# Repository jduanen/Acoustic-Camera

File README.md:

# Acoustic Camera — Project Summary

This project involves the design and implementation of a low-cost,
high-performance acoustic camera: i.e., a microphone array computes a power map
of the sound sources in a video camera's field of view and overlays it on the
video in real time.

Uses of such a device include locating vibration, gas leaks and electrical
breakdown, and as a hearing aid for people who can no longer localize sound
with one functional ear.

One of the top-level objectives for this project is to explore the use of
deep-learning models for this application and compare the performance and cost
with that of traditional DSP-based beamforming algorithms.

A full technical overview of the project can be found in [OVERVIEW.md](./OVERVIEW.md);
see the linked documents for more detail.

The Phase 3 prototype (4x4-mic array) unit looks like this:
<br>

This is an animation of the current state of the Phase 4 (96-mic spiral array) version's PCBs: 

See an example of a commercial product here [Fluke](https://youtu.be/UPVcwDzhBZ8) and a low-cost consumer product here [Fotric](https://youtu.be/MBhJoPzHv2Y)

## How it works

The microphone array samples the sound field at every mic at once. For each candidate direction
(azimuth, elevation), a **steering vector** describes the expected phase pattern across the
mics; a **beamformer** scores each direction against the measured **cross-spectral matrix
(CSM)** and the scores form the energy map overlaid on the video.

Three array properties set performance:

| Property | Controls | Rule |
|---|---|---|
| Aperture *D* | Beam width (resolution) and low-frequency limit | HPBW ≈ 58° × λ/*D*; useful directionality needs *f* > *c*/*D* |
| Minimum mic spacing *d* | High-frequency limit (grating lobes above it) | *f*<sub>Nyq</sub> = *c* / (2*d*) |
| Mic layout and count | Sidelobe level (MSL), SNR | Irregular spacing suppresses aliasing; more mics lower sidelobes |

Other key ideas: far field begins at *r* > 2*D*²/λ; the **point spread function** is how the
array smears a point source; commercial cameras average power incoherently across an octave
band to cut noise. Details: [BACKGROUND.md](./BACKGROUND.md), [MIC_ARRAYS.md](./MIC_ARRAYS.md).

**Algorithms explored** (one per family): Delay-and-Sum (simple, robust, wide beam), MVDR
(adaptive, suppresses interferers), CLEAN-SC (deconvolution, removes PSF artifacts), MUSIC
(subspace, super-resolution when the source count is known). ML methods come in Phase 5.

## Requirements and key design choices

| Parameter | Target |
|---|---|
| Frequency range | 200 Hz: 8 kHz (useful imaging from ~2 kHz) |
| Resolution (HPBW) | ~9.4° @ 8 kHz, ~19° @ 4 kHz, ~82° @ 1 kHz (simulated, Phase 4 array) |
| Distance | ~0.5 m (far-field limit) to ~10 m |
| Field of view | ±45° H, ±30° V, matched to the camera |
| Array | ~300 mm aperture, 96 MEMS mics, Underbrink 12 × 8 log-spiral, 12.94 mm min spacing (Nyquist ≈ 13.3 kHz) |

Why these numbers ([TRADEOFFS.md](./TRADEOFFS.md)):
- **300 mm aperture** is the practical sweet spot: portable, yet ~9° at 8 kHz. 5° at 1 kHz
  would need a ~4 m aperture.
- **96 mics** matches commercial practice (gfai Mikado uses 96 in the same pattern). Mic count
  grows as (aperture/spacing)², so going much smaller in spacing costs ~400+ mics.
- **Underbrink spiral** gave the best sidelobe suppression of all patterns simulated
  (−24.4 dB @ 4 kHz), with circular symmetry.
- **Beamforming grid**: 2–3 points per HPBW is enough. Finer grids cost memory and time
  (the steering matrix dominates) without improving resolution; the 96-mic array needs a
  finer grid than the UMA-16's 0.5°–1°.

## Development phases

Each phase delivers a working end-to-end system ([PLAN.md](./PLAN.md)).

| Phase | Hardware | Goal | Status |
|---|---|---|---|
| 1 | Simulation | Validate algorithms and array geometry | Complete |
| 2 | ReSpeaker XVF3800 (4 mics, 90 mm) | First end-to-end pipeline: capture → beamform → overlay | Complete |
| 3 | miniDSP UMA-16 v2 (16 mics, 126 mm) | 2D (az × el) beamforming, calibration, touch UI | Complete |
| 4 | Custom PCBs (96 mics, 300 mm, FPGA) | Full-performance system | In progress |
| 5 | Phase 3/4 hardware | ML beamformer (PILOT / CRNN) vs CLEAN-SC | Not started |

### Phase 1 — simulation ([PHASE1.md](./PHASE1.md))
- Recommended array: Underbrink 12 × 8, α = 22°, 96 mics, 300 mm, 12.9 mm minimum spacing, alias-free to ~13 kHz.
- HPBW: >180° below 500 Hz, ~82° @ 1 kHz, ~37° @ 2 kHz, ~19° @ 4 kHz, ~9° @ 8 kHz.
- Algorithm choice: CLEAN-SC for real-time single-source display; MVDR for multiple or weak
  sources; MUSIC for closely spaced sources with known count; D&S for lowest latency.
  256 snapshots per CSM.
- Works well: industrial source hunting at 2–8 kHz, multi-source scenes, normal rooms,
  near field at 0.5–3 m. Not suited: below 1 kHz, very reverberant spaces (DRR < 3 dB),
  separating sources on the same bearing, MUSIC at SNR < 10 dB.

### Phase 2 — ReSpeaker smoke test ([PHASE2.md](./PHASE2.md))
- Raw mics are USB channels 2–5; gain imbalance up to ~3.6× motivated calibration.
- D&S, MVDR and CLEAN-SC agreed within 5°. Live script: `src/acoustic_camera_p2.py`.

### Phase 3 — UMA-16 ([PHASE3.md](./PHASE3.md))
- 16 channels at 48 kHz, 2D beamforming with full-frame overlay on webcam or Pi camera.
- Live script `src/acoustic_camera_p3.py` with a touch UI: frequency sliders and spectrum
  pan, energy threshold (auto/manual), zoom/recenter/dwell, power indicator, saved settings.
- Shared math in `src/beamforming.py` (pytest suite in `tests/`); `src/benchmark_algos.py`
  measures per-algorithm cost. A 1°/pt grid brings all four algorithms within 20 fps.
- Lesson: the UMA-16's usable window is only ~2–4 kHz, bounded by aperture below and
  spatial Nyquist above.

### Phase 4 — custom hardware ([PHASE4.md](./PHASE4.md))
96-mic Underbrink spiral, 12 arms × 8 mics, with PDM → CIC/FIR decimation in an FPGA and
data streamed to a host (96 ch × 48 kHz × 24 bit ≈ 110 Mbit/s, within 1 GbE). A Pi Camera
Module 3 Wide mounts through the centre of the array.

- **Single-FPGA design (primary).** One ALINX AC7200 module (Xilinx XC7A200T) runs all 96
  channels plus a GbE/UDP link. RTL is done and fits (43.5% LUTs for the pipeline, 48.1% with
  the GbE MAC and packetizer). Two boards:
  - `mic_array`: Ø320 mm, 96 Infineon IM72D128 mics, TCXO and clock tree, local 3.3 V LDOs.
  - `front_end`: AC7200 module, power regulation, DP83867 GbE PHY.
  - Joined by Panasonic P5KS board-to-board connectors (9 mm mated height).
  - Status: the current Phase 4 design; PCBs being laid out and prepared for fabrication. See
    [pcb/SCHEMATIC_NOTES.md](./pcb/SCHEMATIC_NOTES.md) for the current schematic, power and
    connector details.
- **Multi-FPGA alternate.** Four Cmod A7-35T cluster boards (24 mics each) feed a hub board
  over a shared-clock spoke bus; the hub relays to a Raspberry Pi 5 over USB. Breadboarded
  and laid out as PCBs, but the boards were never built.

### Phase 5 — ML
Needs real Phase 3/4 data to train and validate models.

## Landscape

- **Commercial products** ([PRODUCTS.md](./PRODUCTS.md)): 64–96 MEMS mics is the sweet spot
  for handheld far-field use; USB for portable, PoE for fixed installs; a co-located video
  camera at the array centre is universal.
- **Open-source projects** ([PROJECTS.md](./PROJECTS.md)): FPGA → GbE → GPU host is the
  established pattern above ~96 mics; cross-correlation calibration with GPU gradient descent
  (Ben Wang) recovers mic positions and speed of sound. This project uses **Acoular** (Python)
  for parts of its beamforming work.

## Open questions and TODOs

- Match camera optics to the array's FOV and resolution
- Partition processing between FPGA and host; choose final processing/display hardware
- Packaging; low-noise audio front-end layout
- Add-on arms to extend the aperture for better low-frequency resolution

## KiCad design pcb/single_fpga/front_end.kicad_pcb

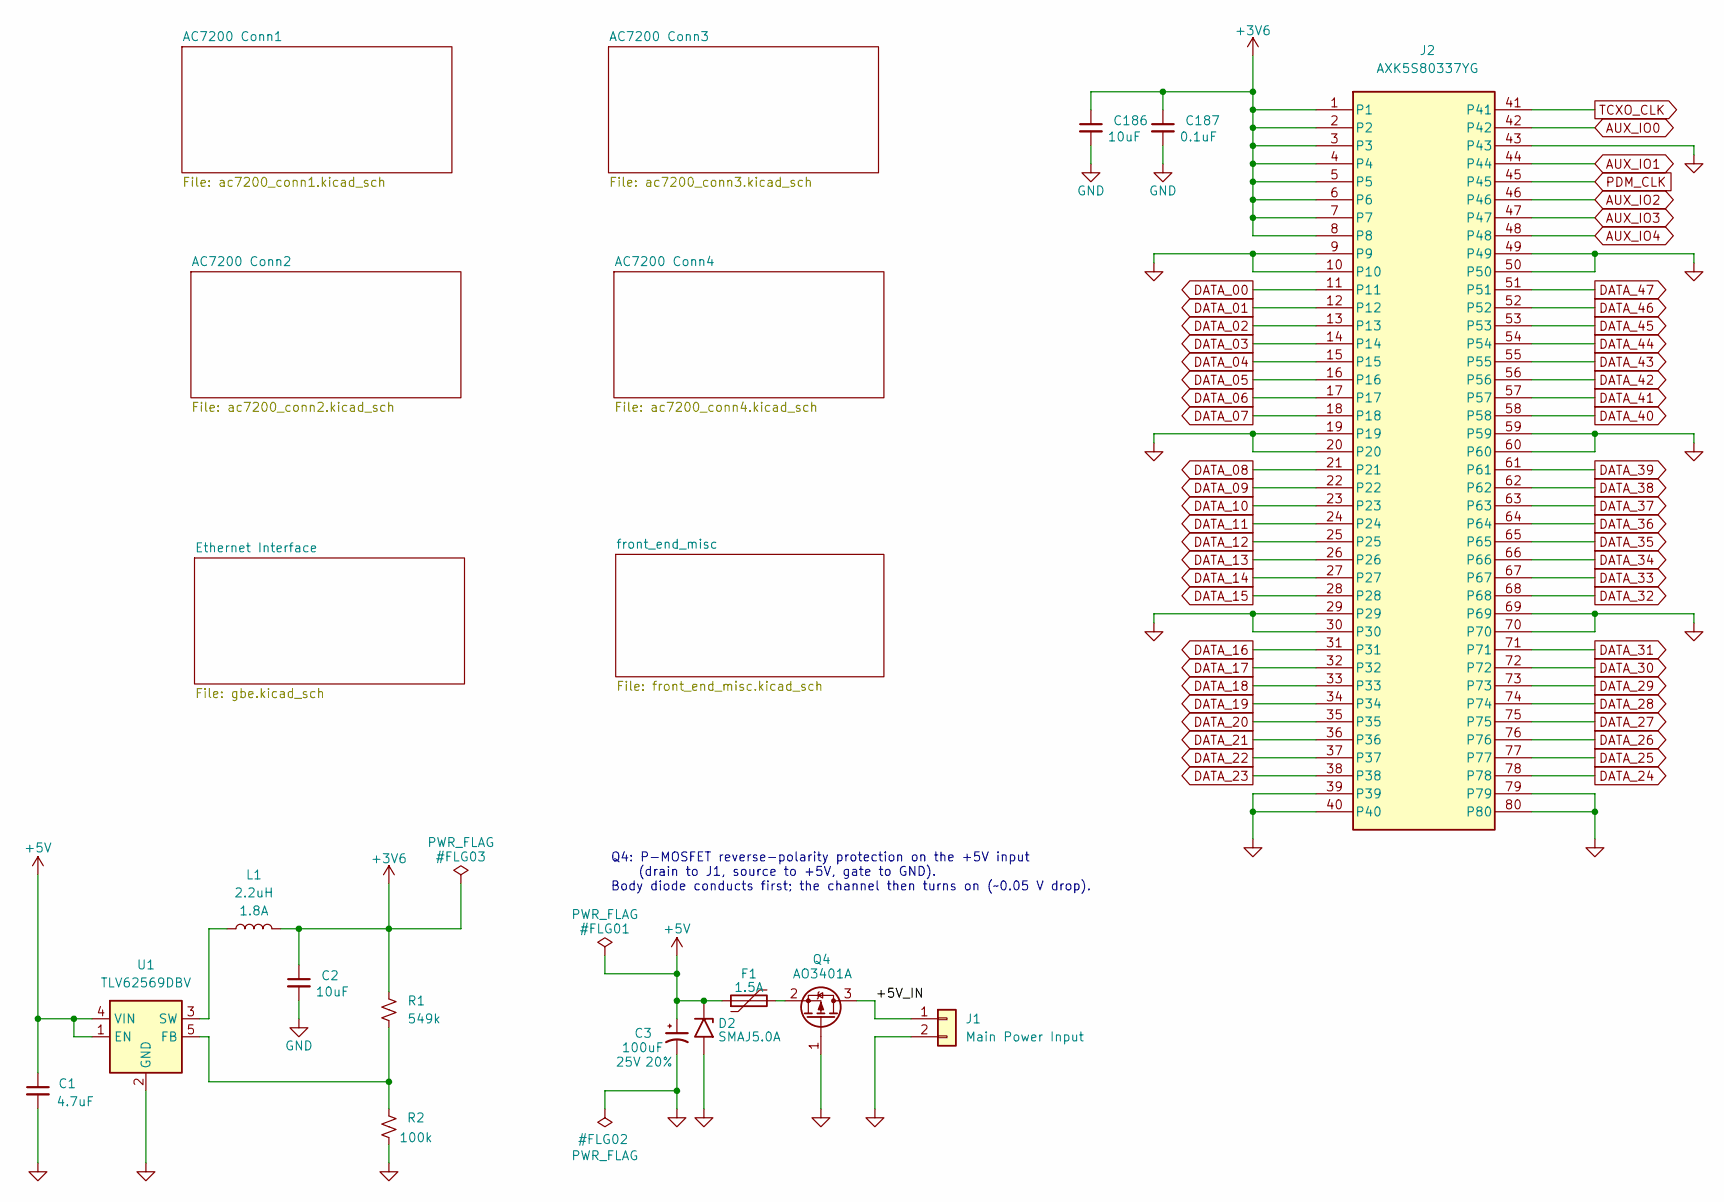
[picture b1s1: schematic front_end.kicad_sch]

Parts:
C1: 4.7uF; C_0805_2012Metric; Voltage 16V; Tolerance 10%; Part Number CL21B475KOFNNNE; LCSC Part # C107365
C2, C186: 10uF; C_0805_2012Metric; Voltage 10V; Tolerance 10%; Part Number GRM21BR71A106KE51L; LCSC Part # C86038
C3: 100uF; CP_Elec_6.3x5.8; Voltage 25V; Tolerance 20%; Part Number FVM025ADA101M0654; LCSC Part # C7469933
C187: 0.1uF; C_0402_1005Metric; Voltage 16V; Tolerance 10%; Part Number CL05B104KO5NNNC; LCSC Part # C1525
D2: SMAJ5.0A; D_SMA; Part Number SMAJ5.0A; LCSC Part # C83329
F1: 1.5A; Fuse_1206_3216Metric; Part Number BSMD1206-150-16V; LCSC Part # C883133
J1: Main Power Input; JST_XH_B2B-XH-A_1x02_P2.50mm_Vertical; Part Number B2B-XH-A(LF)(SN); LCSC Part # C158012
J2: AXK5S80337YG; Part Number AXK5S80337YG; LCSC Part # C5572475
L1: 2.2uH; L_Murata_DFE201610P; Part Number DFE201612E-2R2M=P2; LCSC Part # C337893
Q4: AO3401A; SOT-23; Part Number AO3401A; LCSC Part # C15127
R1: 549k; R_0603_1608Metric; Tolerance 1%; Part Number RC0603FR-07549KL; LCSC Part # C245978
R2: 100k; R_0603_1608Metric; Tolerance 1%; Part Number 0603WAF1003T5E; LCSC Part # C25803
U1: TLV62569DBV; SOT-23-5; Part Number TLV62569DBVR; LCSC Part # C141836

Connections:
+3V6: C2.1, C186.1, C187.1, J2.1, J2.2, J2.3, J2.4, J2.5, J2.6, J2.7, J2.8, L1.2, R1.1; also elsewhere on the board
+5V: C1.1, C3.1, D2.1 (A1), F1.1, U1.1 (EN), U1.4 (VIN); also elsewhere on the board
/+5V_IN: J1.1, Q4.3 (D)
AUX_IO0: J2.42; also elsewhere on the board
AUX_IO1: J2.44; also elsewhere on the board
AUX_IO2: J2.46; also elsewhere on the board
AUX_IO3: J2.47; also elsewhere on the board
AUX_IO4: J2.48; also elsewhere on the board
DATA_00: J2.11; also elsewhere on the board
DATA_01: J2.12; also elsewhere on the board
DATA_02: J2.13; also elsewhere on the board
DATA_03: J2.14; also elsewhere on the board
DATA_04: J2.15; also elsewhere on the board
DATA_05: J2.16; also elsewhere on the board
DATA_06: J2.17; also elsewhere on the board
DATA_07: J2.18; also elsewhere on the board
DATA_08: J2.21; also elsewhere on the board
DATA_09: J2.22; also elsewhere on the board
DATA_10: J2.23; also elsewhere on the board
DATA_11: J2.24; also elsewhere on the board
DATA_12: J2.25; also elsewhere on the board
DATA_13: J2.26; also elsewhere on the board
DATA_14: J2.27; also elsewhere on the board
DATA_15: J2.28; also elsewhere on the board
DATA_16: J2.31; also elsewhere on the board
DATA_17: J2.32; also elsewhere on the board
DATA_18: J2.33; also elsewhere on the board
DATA_19: J2.34; also elsewhere on the board
DATA_20: J2.35; also elsewhere on the board
DATA_21: J2.36; also elsewhere on the board
DATA_22: J2.37; also elsewhere on the board
DATA_23: J2.38; also elsewhere on the board
DATA_24: J2.78; also elsewhere on the board
DATA_25: J2.77; also elsewhere on the board
DATA_26: J2.76; also elsewhere on the board
DATA_27: J2.75; also elsewhere on the board
DATA_28: J2.74; also elsewhere on the board
DATA_29: J2.73; also elsewhere on the board
DATA_30: J2.72; also elsewhere on the board
DATA_31: J2.71; also elsewhere on the board
DATA_32: J2.68; also elsewhere on the board
DATA_33: J2.67; also elsewhere on the board
DATA_34: J2.66; also elsewhere on the board
DATA_35: J2.65; also elsewhere on the board
DATA_36: J2.64; also elsewhere on the board
DATA_37: J2.63; also elsewhere on the board
DATA_38: J2.62; also elsewhere on the board
DATA_39: J2.61; also elsewhere on the board
DATA_40: J2.58; also elsewhere on the board
DATA_41: J2.57; also elsewhere on the board
DATA_42: J2.56; also elsewhere on the board
DATA_43: J2.55; also elsewhere on the board
DATA_44: J2.54; also elsewhere on the board
DATA_45: J2.53; also elsewhere on the board
DATA_46: J2.52; also elsewhere on the board
DATA_47: J2.51; also elsewhere on the board
GND: C1.2, C2.2, C3.2, C186.2, C187.2, D2.2 (A2), J1.2, J2.9, J2.10, J2.19, J2.20, J2.29, J2.30, J2.39, J2.40, J2.43, J2.49, J2.50, J2.59, J2.60, J2.69, J2.70, J2.79, J2.80, Q4.1 (G), R2.1, U1.2 (GND); also elsewhere on the board
unnamed: F1.2, Q4.2 (S)
unnamed: R1.2, R2.2, U1.5 (FB)
unnamed: L1.1, U1.3 (SW)
PDM_CLK: J2.45; also elsewhere on the board
TCXO_CLK: J2.41; also elsewhere on the board

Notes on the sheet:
Q4: P-MOSFET reverse-polarity protection on the +5V input (drain to J1, source to +5V, gate to GND). Body diode conducts first; the channel then turns on (~0.05 V drop).

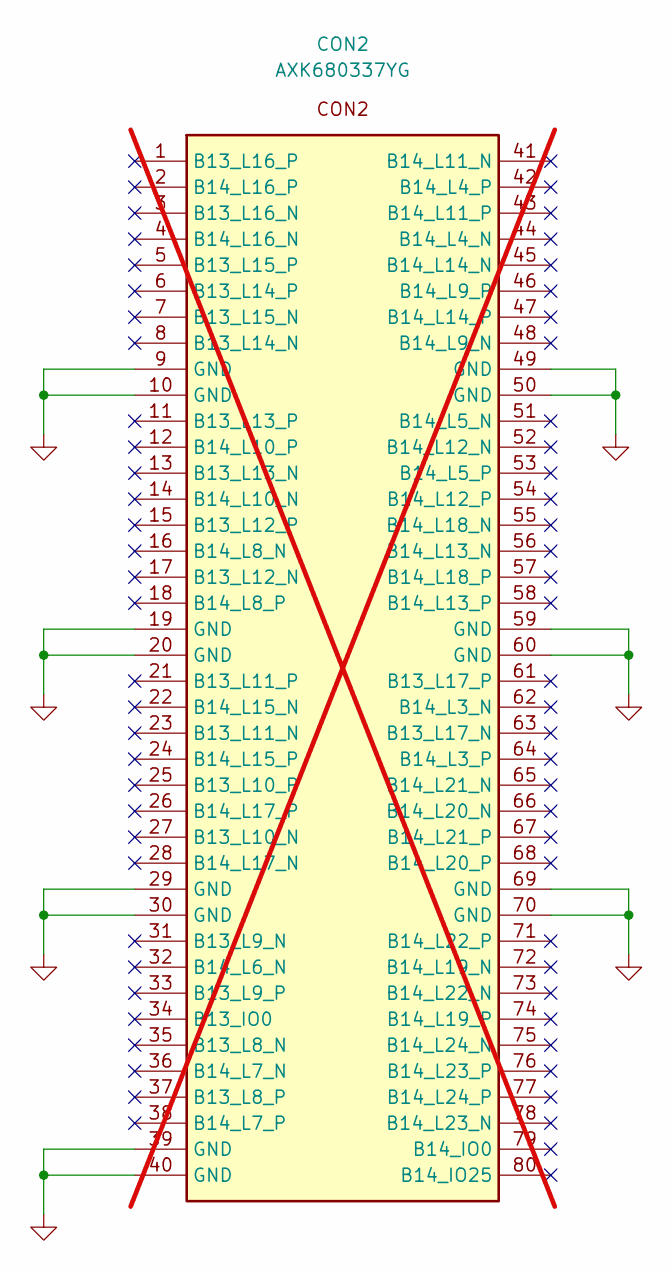
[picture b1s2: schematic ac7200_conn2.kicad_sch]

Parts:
CON2: AXK680337YG; Part Number AXK680337YG; LCSC Part # C2848859; not fitted

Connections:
GND: CON2.9 (GND), CON2.10 (GND), CON2.19 (GND), CON2.20 (GND), CON2.29 (GND), CON2.30 (GND), CON2.39 (GND), CON2.40 (GND), CON2.49 (GND), CON2.50 (GND), CON2.59 (GND), CON2.60 (GND), CON2.69 (GND), CON2.70 (GND); also elsewhere on the board

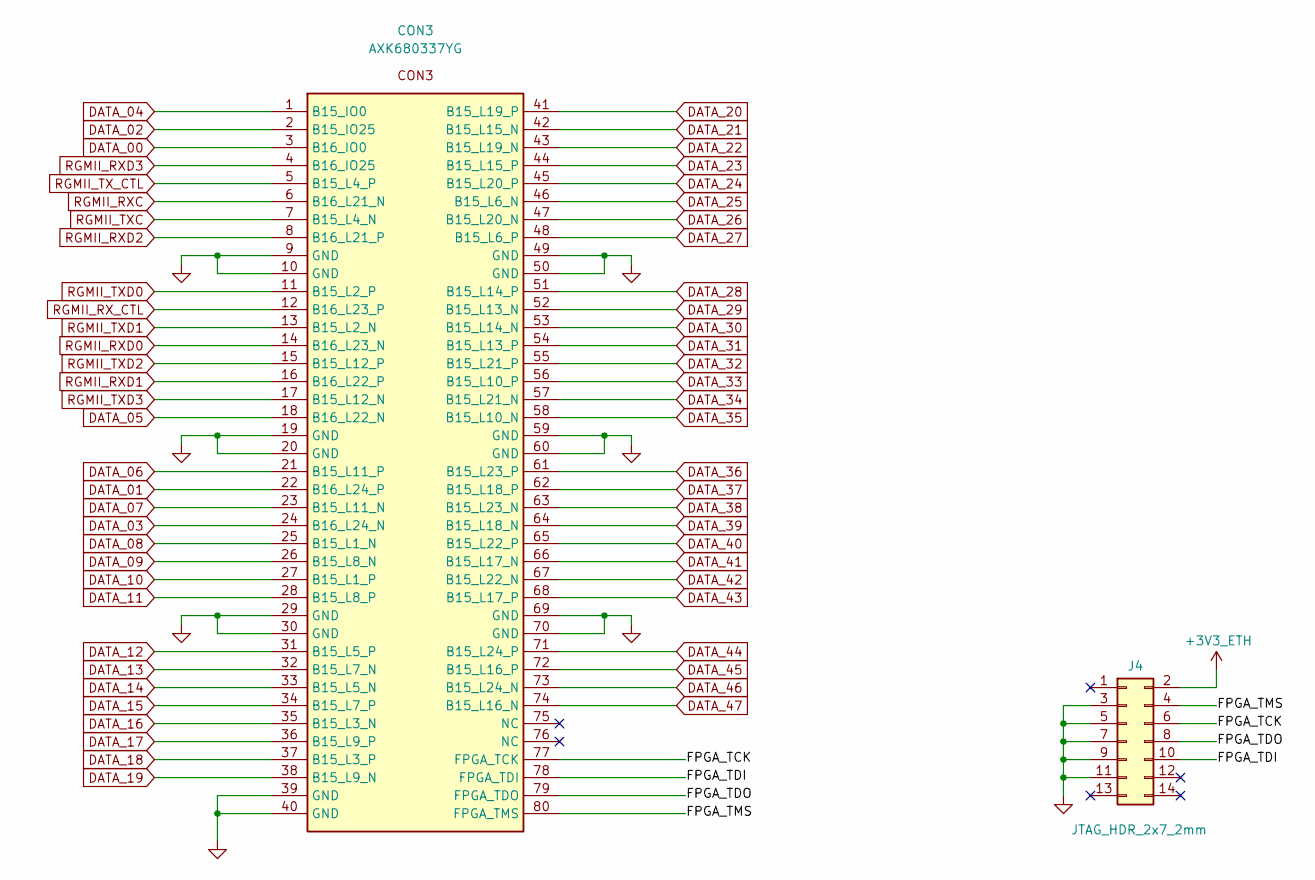
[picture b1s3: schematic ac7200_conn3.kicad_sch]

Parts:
CON3: AXK680337YG; Part Number AXK680337YG; LCSC Part # C2848859
J4: JTAG_HDR_2x7_2mm; PinHeader_2x07_P2.00mm_Vertical; Part Number PZ200-2-07-Z; LCSC Part # C2905993

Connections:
+3V3_ETH: J4.2; also elsewhere on the board
/AC7200 Conn3/FPGA_TCK: CON3.77 (FPGA_TCK), J4.6
/AC7200 Conn3/FPGA_TDI: CON3.78 (FPGA_TDI), J4.10
/AC7200 Conn3/FPGA_TDO: CON3.79 (FPGA_TDO), J4.8
/AC7200 Conn3/FPGA_TMS: CON3.80 (FPGA_TMS), J4.4
DATA_00: CON3.3 (B16_IO0); also elsewhere on the board
DATA_01: CON3.22 (B16_L24_P); also elsewhere on the board
DATA_02: CON3.2 (B15_IO25); also elsewhere on the board
DATA_03: CON3.24 (B16_L24_N); also elsewhere on the board
DATA_04: CON3.1 (B15_IO0); also elsewhere on the board
DATA_05: CON3.18 (B16_L22_N); also elsewhere on the board
DATA_06: CON3.21 (B15_L11_P); also elsewhere on the board
DATA_07: CON3.23 (B15_L11_N); also elsewhere on the board
DATA_08: CON3.25 (B15_L1_N); also elsewhere on the board
DATA_09: CON3.26 (B15_L8_N); also elsewhere on the board
DATA_10: CON3.27 (B15_L1_P); also elsewhere on the board
DATA_11: CON3.28 (B15_L8_P); also elsewhere on the board
DATA_12: CON3.31 (B15_L5_P); also elsewhere on the board
DATA_13: CON3.32 (B15_L7_N); also elsewhere on the board
DATA_14: CON3.33 (B15_L5_N); also elsewhere on the board
DATA_15: CON3.34 (B15_L7_P); also elsewhere on the board
DATA_16: CON3.35 (B15_L3_N); also elsewhere on the board
DATA_17: CON3.36 (B15_L9_P); also elsewhere on the board
DATA_18: CON3.37 (B15_L3_P); also elsewhere on the board
DATA_19: CON3.38 (B15_L9_N); also elsewhere on the board
DATA_20: CON3.41 (B15_L19_P); also elsewhere on the board
DATA_21: CON3.42 (B15_L15_N); also elsewhere on the board
DATA_22: CON3.43 (B15_L19_N); also elsewhere on the board
DATA_23: CON3.44 (B15_L15_P); also elsewhere on the board
DATA_24: CON3.45 (B15_L20_P); also elsewhere on the board
DATA_25: CON3.46 (B15_L6_N); also elsewhere on the board
DATA_26: CON3.47 (B15_L20_N); also elsewhere on the board
DATA_27: CON3.48 (B15_L6_P); also elsewhere on the board
DATA_28: CON3.51 (B15_L14_P); also elsewhere on the board
DATA_29: CON3.52 (B15_L13_N); also elsewhere on the board
DATA_30: CON3.53 (B15_L14_N); also elsewhere on the board
DATA_31: CON3.54 (B15_L13_P); also elsewhere on the board
DATA_32: CON3.55 (B15_L21_P); also elsewhere on the board
DATA_33: CON3.56 (B15_L10_P); also elsewhere on the board
DATA_34: CON3.57 (B15_L21_N); also elsewhere on the board
DATA_35: CON3.58 (B15_L10_N); also elsewhere on the board
DATA_36: CON3.61 (B15_L23_P); also elsewhere on the board
DATA_37: CON3.62 (B15_L18_P); also elsewhere on the board
DATA_38: CON3.63 (B15_L23_N); also elsewhere on the board
DATA_39: CON3.64 (B15_L18_N); also elsewhere on the board
DATA_40: CON3.65 (B15_L22_P); also elsewhere on the board
DATA_41: CON3.66 (B15_L17_N); also elsewhere on the board
DATA_42: CON3.67 (B15_L22_N); also elsewhere on the board
DATA_43: CON3.68 (B15_L17_P); also elsewhere on the board
DATA_44: CON3.71 (B15_L24_P); also elsewhere on the board
DATA_45: CON3.72 (B15_L16_P); also elsewhere on the board
DATA_46: CON3.73 (B15_L24_N); also elsewhere on the board
DATA_47: CON3.74 (B15_L16_N); also elsewhere on the board
GND: CON3.9 (GND), CON3.10 (GND), CON3.19 (GND), CON3.20 (GND), CON3.29 (GND), CON3.30 (GND), CON3.39 (GND), CON3.40 (GND), CON3.49 (GND), CON3.50 (GND), CON3.59 (GND), CON3.60 (GND), CON3.69 (GND), CON3.70 (GND), J4.3, J4.5, J4.7, J4.9, J4.11; also elsewhere on the board
RGMII_RXC: CON3.6 (B16_L21_N); also elsewhere on the board
RGMII_RXD0: CON3.14 (B16_L23_N); also elsewhere on the board
RGMII_RXD1: CON3.16 (B16_L22_P); also elsewhere on the board
RGMII_RXD2: CON3.8 (B16_L21_P); also elsewhere on the board
RGMII_RXD3: CON3.4 (B16_IO25); also elsewhere on the board
RGMII_RX_CTL: CON3.12 (B16_L23_P); also elsewhere on the board
RGMII_TXC: CON3.7 (B15_L4_N); also elsewhere on the board
RGMII_TXD0: CON3.11 (B15_L2_P); also elsewhere on the board
RGMII_TXD1: CON3.13 (B15_L2_N); also elsewhere on the board
RGMII_TXD2: CON3.15 (B15_L12_P); also elsewhere on the board
RGMII_TXD3: CON3.17 (B15_L12_N); also elsewhere on the board
RGMII_TX_CTL: CON3.5 (B15_L4_P); also elsewhere on the board

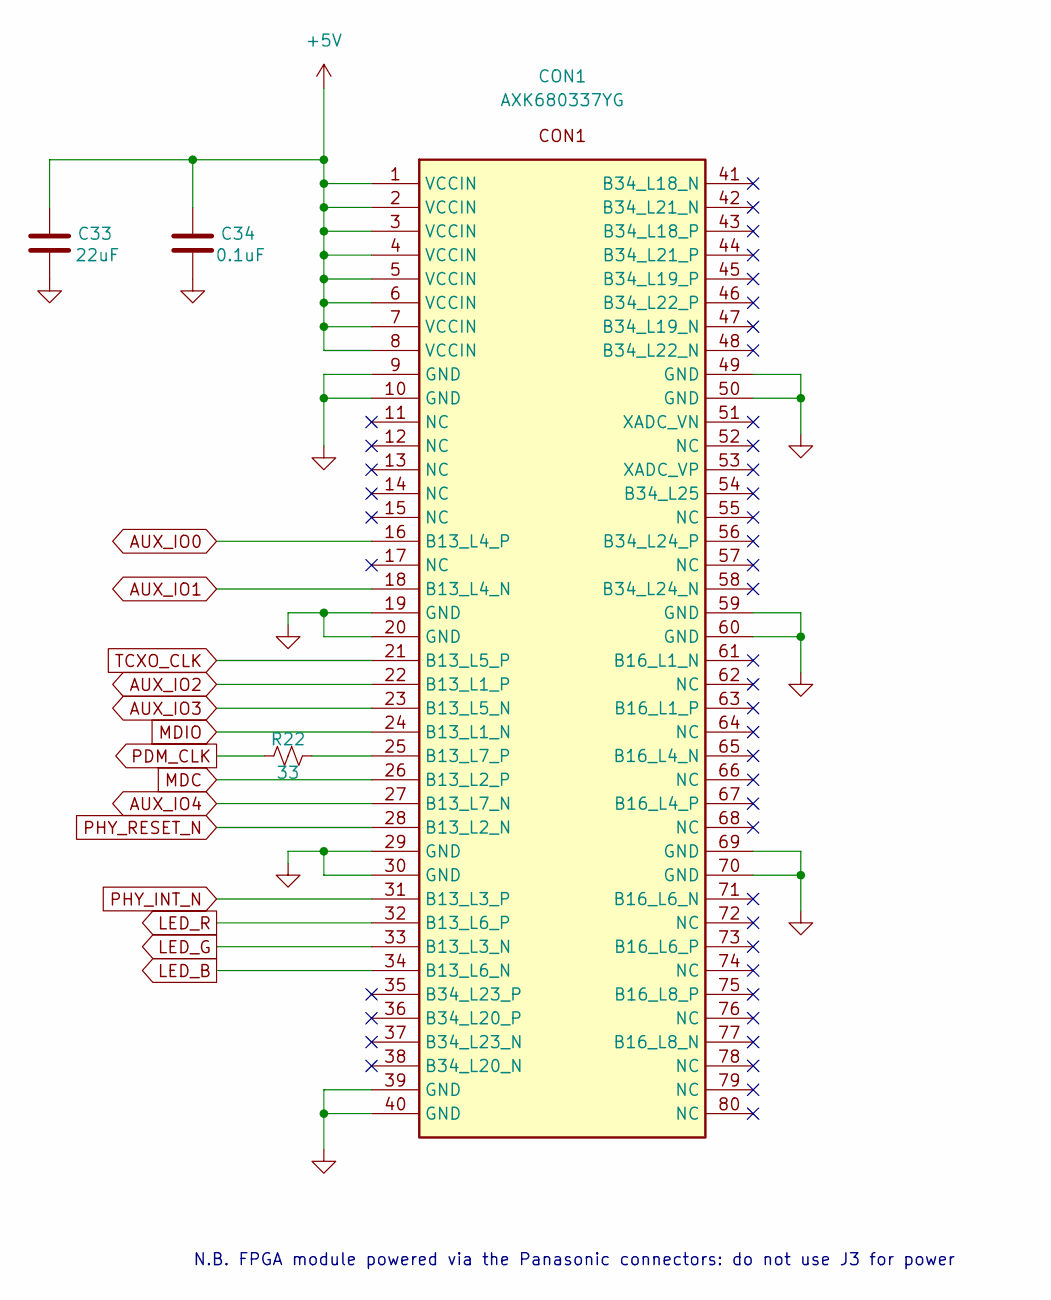
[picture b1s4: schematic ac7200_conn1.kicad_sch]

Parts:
C33: 22uF; C_0805_2012Metric; Part Number CL21A226MAQNNNE; LCSC Part # C45783
C34: 0.1uF; C_0402_1005Metric; Part Number CL05B104KO5NNNC; LCSC Part # C1525
CON1: AXK680337YG; Part Number AXK680337YG; LCSC Part # C2848859
R22: 33; R_0402_1005Metric; Part Number 0402WGF330JTCE; LCSC Part # C25105

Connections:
+5V: C33.1, C34.1, CON1.1 (VCCIN), CON1.2 (VCCIN), CON1.3 (VCCIN), CON1.4 (VCCIN), CON1.5 (VCCIN), CON1.6 (VCCIN), CON1.7 (VCCIN), CON1.8 (VCCIN); also elsewhere on the board
AUX_IO0: CON1.16 (B13_L4_P); also elsewhere on the board
AUX_IO1: CON1.18 (B13_L4_N); also elsewhere on the board
AUX_IO2: CON1.22 (B13_L1_P); also elsewhere on the board
AUX_IO3: CON1.23 (B13_L5_N); also elsewhere on the board
AUX_IO4: CON1.27 (B13_L7_N); also elsewhere on the board
GND: C33.2, C34.2, CON1.9 (GND), CON1.10 (GND), CON1.19 (GND), CON1.20 (GND), CON1.29 (GND), CON1.30 (GND), CON1.39 (GND), CON1.40 (GND), CON1.49 (GND), CON1.50 (GND), CON1.59 (GND), CON1.60 (GND), CON1.69 (GND), CON1.70 (GND); also elsewhere on the board
LED_B: CON1.34 (B13_L6_N); also elsewhere on the board
LED_G: CON1.33 (B13_L3_N); also elsewhere on the board
LED_R: CON1.32 (B13_L6_P); also elsewhere on the board
MDC: CON1.26 (B13_L2_P); also elsewhere on the board
MDIO: CON1.24 (B13_L1_N); also elsewhere on the board
unnamed: CON1.25 (B13_L7_P), R22.2
PDM_CLK: R22.1; also elsewhere on the board
PHY_INT_N: CON1.31 (B13_L3_P); also elsewhere on the board
PHY_RESET_N: CON1.28 (B13_L2_N); also elsewhere on the board
TCXO_CLK: CON1.21 (B13_L5_P); also elsewhere on the board

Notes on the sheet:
N.B. FPGA module powered via the Panasonic connectors: do not use J3 for power

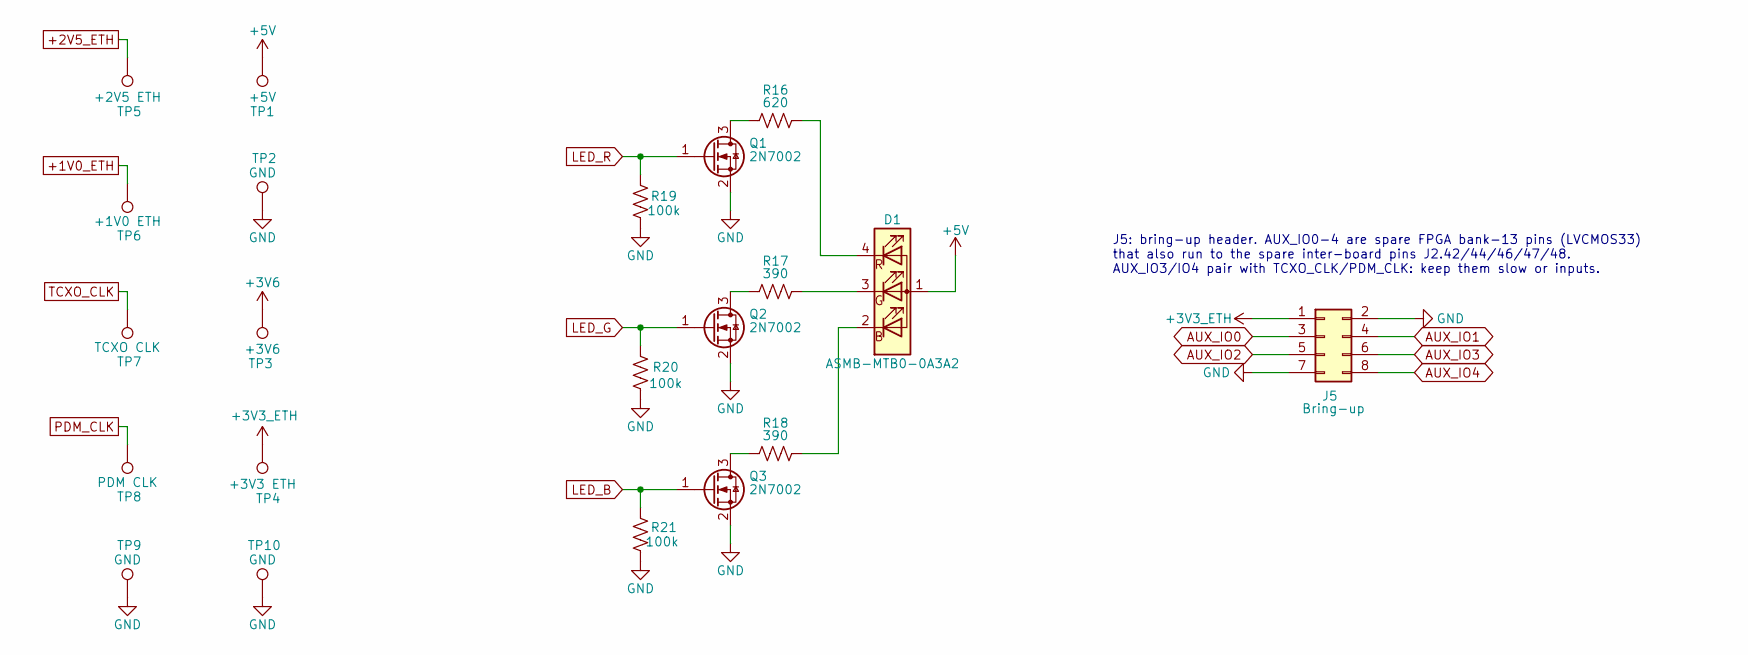
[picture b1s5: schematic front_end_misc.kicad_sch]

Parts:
D1: ASMB-MTB0-0A3A2; LED_Avago_PLCC4_3.2x2.8mm_CW; Part Number ASMB-MTB0-0A3A2; LCSC Part # C2686824
J5: Bring-up; PinHeader_2x04_P2.54mm_Vertical; Part Number HX PZ2.54-2x4P ZZ; LCSC Part # C32713277
Q1, Q2, Q3: 2N7002; SOT-23; Part Number 2N7002; LCSC Part # C8545
R16: 620; R_0603_1608Metric; Part Number 0603WAF6200T5E; LCSC Part # C23220
R17, R18: 390; R_0603_1608Metric; Part Number 0603WAF3900T5E; LCSC Part # C23151
R19, R20, R21: 100k; R_0603_1608Metric; Part Number 0603WAF1003T5E; LCSC Part # C25803
TP1: +5V; TestPoint_THTPad_D2.0mm_Drill1.0mm
TP2, TP9, TP10: GND; TestPoint_THTPad_D2.0mm_Drill1.0mm
TP3: +3V6; TestPoint_THTPad_D2.0mm_Drill1.0mm
TP4: +3V3 ETH; TestPoint_THTPad_D2.0mm_Drill1.0mm
TP5: +2V5 ETH; TestPoint_THTPad_D2.0mm_Drill1.0mm
TP6: +1V0 ETH; TestPoint_THTPad_D2.0mm_Drill1.0mm
TP7: TCXO CLK; TestPoint_THTPad_D2.0mm_Drill1.0mm
TP8: PDM CLK; TestPoint_THTPad_D2.0mm_Drill1.0mm

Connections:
+1V0_ETH: TP6.1 (1_1); also elsewhere on the board
+2V5_ETH: TP5.1 (1_1); also elsewhere on the board
+3V3_ETH: J5.1, TP4.1 (1_1); also elsewhere on the board
+3V6: TP3.1 (1_1); also elsewhere on the board
+5V: D1.1 (A), TP1.1 (1_1); also elsewhere on the board
AUX_IO0: J5.3; also elsewhere on the board
AUX_IO1: J5.4; also elsewhere on the board
AUX_IO2: J5.5; also elsewhere on the board
AUX_IO3: J5.6; also elsewhere on the board
AUX_IO4: J5.8; also elsewhere on the board
GND: J5.2, J5.7, Q1.2 (S), Q2.2 (S), Q3.2 (S), R19.1, R20.1, R21.1, TP2.1 (1_1), TP9.1 (1_1), TP10.1 (1_1); also elsewhere on the board
LED_B: Q3.1 (G), R21.2; also elsewhere on the board
LED_G: Q2.1 (G), R20.2; also elsewhere on the board
LED_R: Q1.1 (G), R19.2; also elsewhere on the board
unnamed: D1.2 (BK), R18.1
unnamed: D1.3 (GK), R17.1
unnamed: D1.4 (RK), R16.1
unnamed: Q1.3 (D), R16.2
unnamed: Q2.3 (D), R17.2
unnamed: Q3.3 (D), R18.2
PDM_CLK: TP8.1 (1_1); also elsewhere on the board
TCXO_CLK: TP7.1 (1_1); also elsewhere on the board

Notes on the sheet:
J5: bring-up header. AUX_IO0-4 are spare FPGA bank-13 pins (LVCMOS33) that also run to the spare inter-board pins J2.42/44/46/47/48. AUX_IO3/IO4 pair with TCXO_CLK/PDM_CLK: keep them slow or inputs.

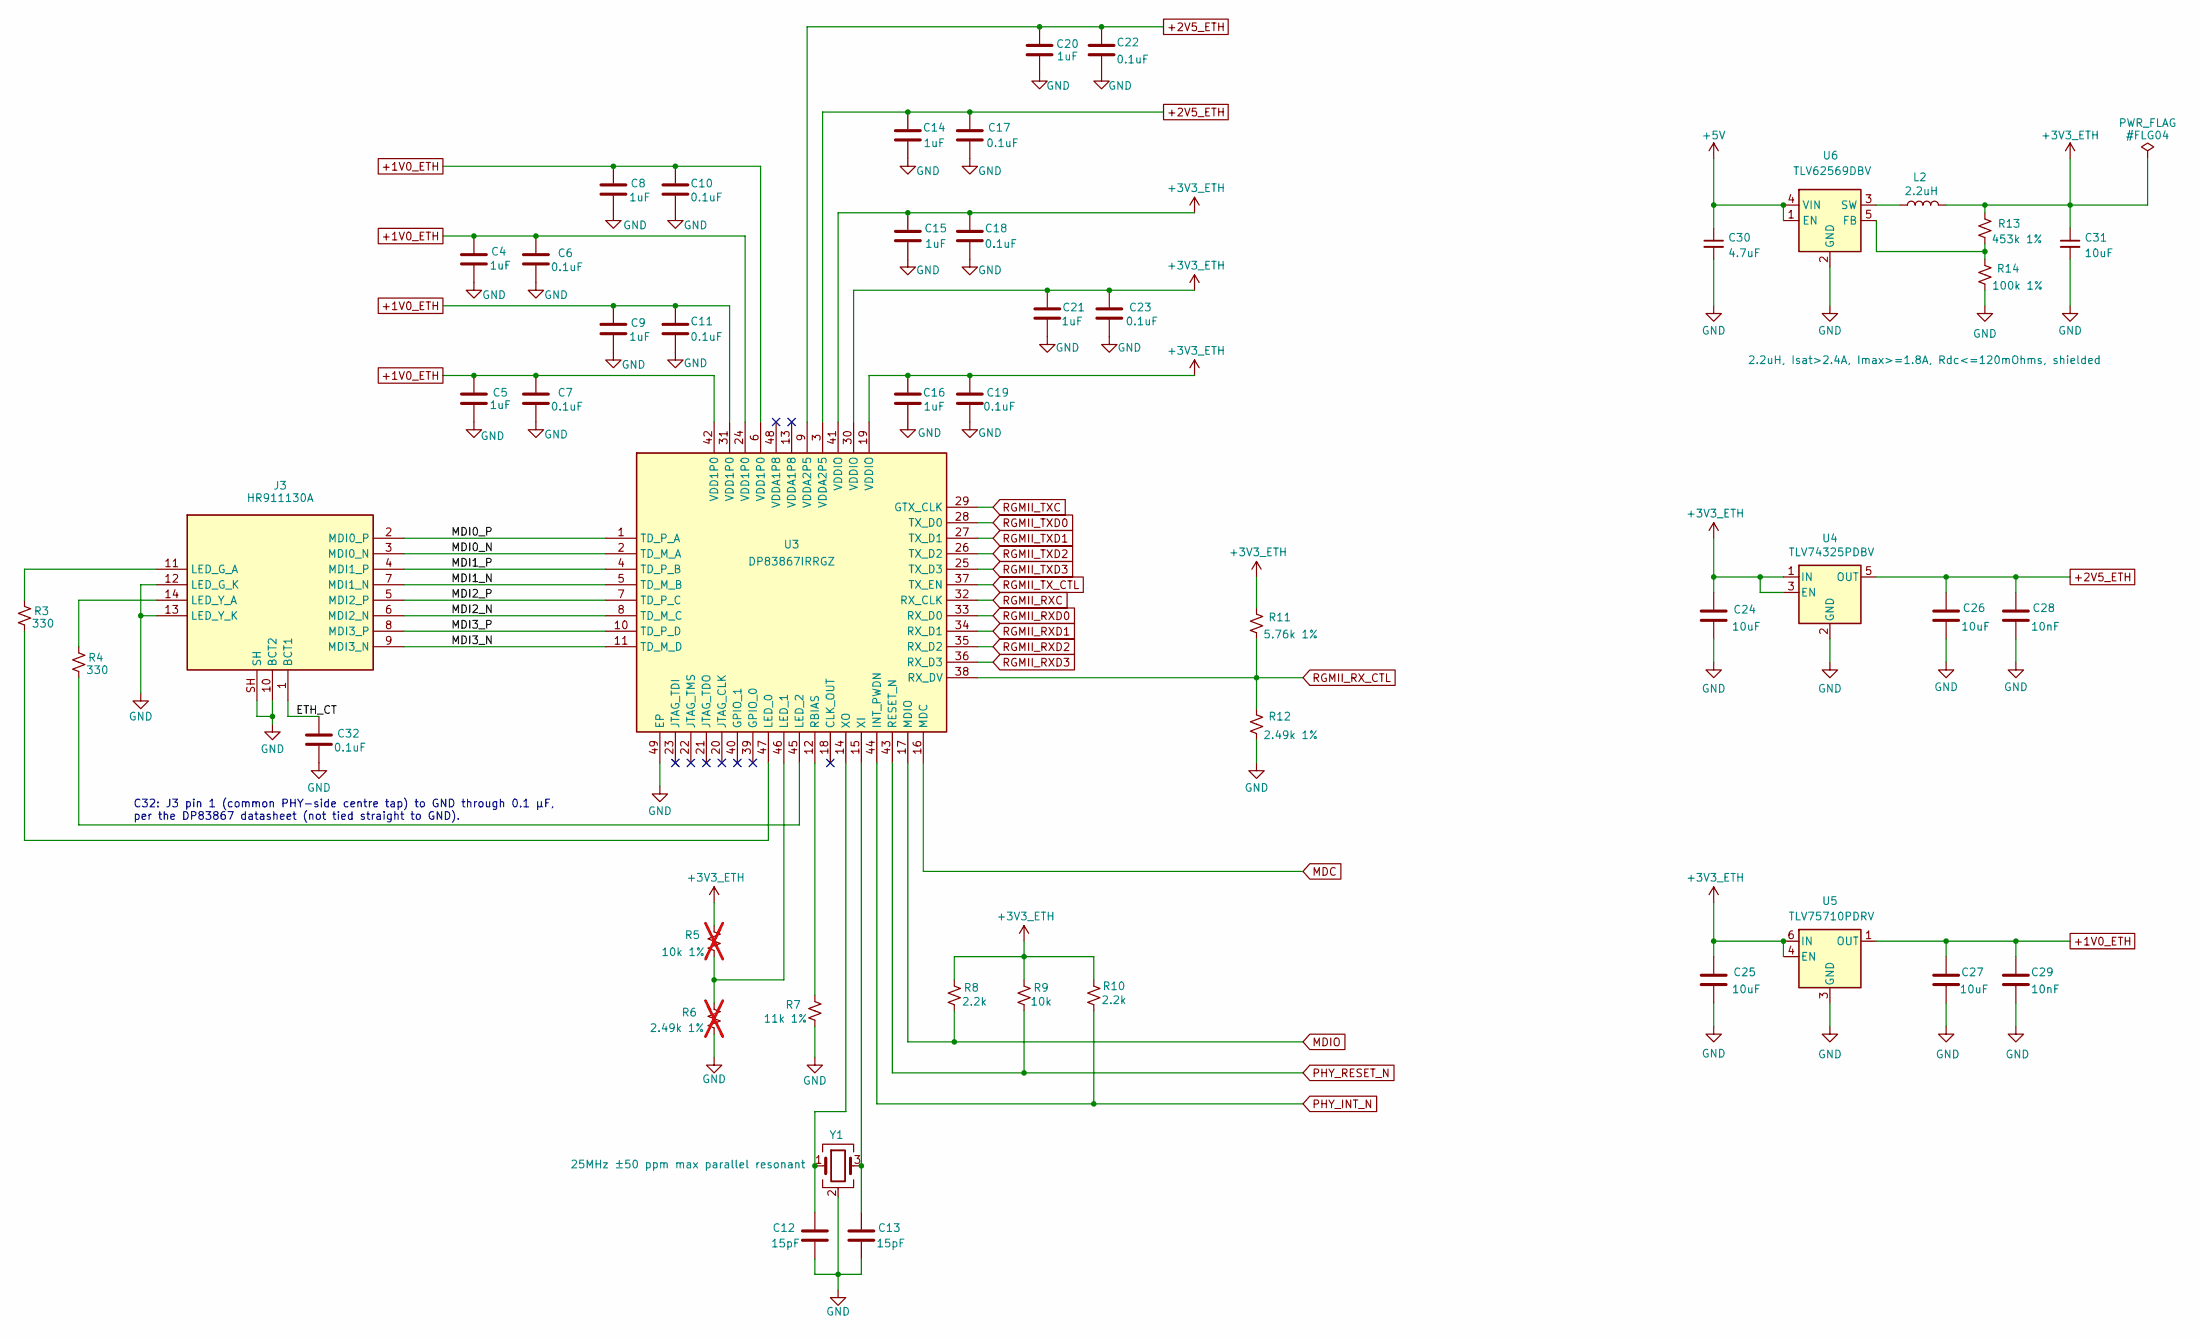
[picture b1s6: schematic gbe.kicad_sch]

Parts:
C4, C5, C8, C9, C14, C15, C16, C20, C21: 1uF; C_0402_1005Metric; Part Number CL05A105KA5NQNC; LCSC Part # C52923
C6, C7, C10, C11, C17, C18, C19, C22, C23, C32: 0.1uF; C_0402_1005Metric; Part Number CL05B104KO5NNNC; LCSC Part # C1525
C12, C13: 15pF; C_0402_1005Metric; Part Number 0402CG150J500NT; LCSC Part # C1548
C24, C25, C26, C27: 10uF; C_0603_1608Metric; Part Number CL10A106KP8NNNC; LCSC Part # C19702
C28, C29: 10nF; C_0603_1608Metric; Part Number 0603B103K500NT; LCSC Part # C57112
C30: 4.7uF; C_0805_2012Metric; Voltage 16V; Tolerance 10%; Part Number CL21B475KOFNNNE; LCSC Part # C107365
C31: 10uF; C_0805_2012Metric; Voltage 10V; Tolerance 10%; Part Number GRM21BR71A106KE51L; LCSC Part # C86038
J3: HR911130A; Part Number HR911130A; LCSC Part # C54408
L2: 2.2uH; L_Murata_DFE201610P; Part Number DFE201612E-2R2M=P2; LCSC Part # C337893
R3, R4: 330; R_0402_1005Metric; Part Number 0402WGF3300TCE; LCSC Part # C25104
R5: 10k 1%; R_0402_1005Metric; not fitted
R6: 2.49k 1%; R_0402_1005Metric; Part Number 0402WGF2491TCE; LCSC Part # C25884; not fitted
R7: 11k 1%; R_0402_1005Metric; Part Number 0402WGF1102TCE; LCSC Part # C25749
R8, R10: 2.2k; R_0402_1005Metric; Part Number 0402WGF2201TCE; LCSC Part # C25879
R9: 10k; R_0402_1005Metric; Part Number 0402WGF1002TCE; LCSC Part # C25744
R11: 5.76k 1%; R_0402_1005Metric; Part Number 0402WGF5761TCE; LCSC Part # C25910
R12: 2.49k 1%; R_0402_1005Metric; Part Number 0402WGF2491TCE; LCSC Part # C25884
R13: 453k 1%; R_0603_1608Metric; Tolerance 1%; Part Number ERJ-3EKF4533V; LCSC Part # C403234
R14: 100k 1%; R_0603_1608Metric; Tolerance 1%; Part Number 0603WAF1003T5E; LCSC Part # C25803
U3: DP83867IRRGZ; VQFN-48-1EP_7x7mm_P0.5mm_EP4.1x4.1mm; Part Number DP83867IRRGZR; LCSC Part # C2678038
U4: TLV74325PDBV; SOT-23-5; Part Number TLV74325PDBVR; LCSC Part # C485154
U5: TLV75710PDRV; WSON-6-1EP_2x2mm_P0.65mm_EP1x1.6mm; Part Number TLV75710PDRVR; LCSC Part # C2861391
U6: TLV62569DBV; SOT-23-5; Part Number TLV62569DBVR; LCSC Part # C141836
Y1: 25MHz ±50 ppm max parallel resonant; Crystal_SMD_3225-4Pin_3.2x2.5mm; Part Number X322525MOB4SI; LCSC Part # C9006

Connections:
+1V0_ETH: C4.1, C5.1, C6.1, C7.1, C8.1, C9.1, C10.1, C11.1, C27.2, C29.2, U3.6 (VDD1P0), U3.24 (VDD1P0), U3.31 (VDD1P0), U3.42 (VDD1P0), U5.1 (OUT); also elsewhere on the board
+2V5_ETH: C14.1, C17.1, C20.1, C22.1, C26.2, C28.2, U3.3 (VDDA2P5), U3.9 (VDDA2P5), U4.5 (OUT); also elsewhere on the board
+3V3_ETH: C15.1, C16.1, C18.1, C19.2, C21.1, C23.1, C24.2, C25.2, C31.1, L2.2, R5.2, R8.1, R9.1, R10.1, R11.2, R13.1, U3.19 (VDDIO), U3.30 (VDDIO), U3.41 (VDDIO), U4.1 (IN), U4.3 (EN), U5.4 (EN), U5.6 (IN); also elsewhere on the board
+5V: C30.1, U6.1 (EN), U6.4 (VIN); also elsewhere on the board
/Ethernet Interface/ETH_CT: C32.1, J3.1 (BCT1)
/Ethernet Interface/MDI0_N: J3.3 (MDI0_N), U3.2 (TD_M_A)
/Ethernet Interface/MDI0_P: J3.2 (MDI0_P), U3.1 (TD_P_A)
/Ethernet Interface/MDI1_N: J3.7 (MDI1_N), U3.5 (TD_M_B)
/Ethernet Interface/MDI1_P: J3.4 (MDI1_P), U3.4 (TD_P_B)
/Ethernet Interface/MDI2_N: J3.6 (MDI2_N), U3.8 (TD_M_C)
/Ethernet Interface/MDI2_P: J3.5 (MDI2_P), U3.7 (TD_P_C)
/Ethernet Interface/MDI3_N: J3.9 (MDI3_N), U3.11 (TD_M_D)
/Ethernet Interface/MDI3_P: J3.8 (MDI3_P), U3.10 (TD_P_D)
GND: C4.2, C5.2, C6.2, C7.2, C8.2, C9.2, C10.2, C11.2, C12.2, C13.2, C14.2, C15.2, C16.2, C17.2, C18.2, C19.1, C20.2, C21.2, C22.2, C23.2, C24.1, C25.1, C26.1, C27.1, C28.1, C29.1, C30.2, C31.2, C32.2, J3.10 (BCT2), J3.12 (LED_G_K), J3.13 (LED_Y_K), J3.SH, R6.1, R7.1, R12.1, R14.1, U3.49 (EP), U4.2 (GND), U5.3 (GND), U5.7 (GND), U6.2 (GND), Y1.2 (G), Y1.4 (G); also elsewhere on the board
MDC: U3.16 (MDC); also elsewhere on the board
MDIO: R8.2, U3.17 (MDIO); also elsewhere on the board
unnamed: J3.11 (LED_G_A), R3.1
unnamed: J3.14 (LED_Y_A), R4.2
unnamed: R3.2, U3.47 (LED_0)
unnamed: R5.1, R6.2, U3.46 (LED_1)
unnamed: R4.1, U3.45 (LED_2)
unnamed: R7.2, U3.12 (RBIAS)
unnamed: C13.1, U3.15 (XI), Y1.3
unnamed: C12.1, U3.14 (XO), Y1.1
unnamed: R13.2, R14.2, U6.5 (FB)
unnamed: L2.1, U6.3 (SW)
PHY_INT_N: R10.2, U3.44 (INT_PWDN); also elsewhere on the board
PHY_RESET_N: R9.2, U3.43 (RESET_N); also elsewhere on the board
RGMII_RXC: U3.32 (RX_CLK); also elsewhere on the board
RGMII_RXD0: U3.33 (RX_D0); also elsewhere on the board
RGMII_RXD1: U3.34 (RX_D1); also elsewhere on the board
RGMII_RXD2: U3.35 (RX_D2); also elsewhere on the board
RGMII_RXD3: U3.36 (RX_D3); also elsewhere on the board
RGMII_RX_CTL: R11.1, R12.2, U3.38 (RX_DV); also elsewhere on the board
RGMII_TXC: U3.29 (GTX_CLK); also elsewhere on the board
RGMII_TXD0: U3.28 (TX_D0); also elsewhere on the board
RGMII_TXD1: U3.27 (TX_D1); also elsewhere on the board
RGMII_TXD2: U3.26 (TX_D2); also elsewhere on the board
RGMII_TXD3: U3.25 (TX_D3); also elsewhere on the board
RGMII_TX_CTL: U3.37 (TX_EN); also elsewhere on the board

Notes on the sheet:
C32: J3 pin 1 (common PHY-side centre tap) to GND through 0.1 µF, per the DP83867 datasheet (not tied straight to GND).
